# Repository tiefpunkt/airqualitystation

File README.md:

# Air Quality Station

Small outdoor particulate matter sensor. Measures PM1.0 and PM2.5, as well as temperature and humidity. Connects to an online service to show the measurements not only of one sensor, but all sensors in the area.

## Hardware
* ESP8266
* [Custom PCB](hardware/) (or your own whatever thingie)
* A bunch of small parts (TODO: Add BOM)
* DHT22 for temperature and humidity ([Grove Wiki](http://www.seeedstudio.com/wiki/Grove_-_Temperature_and_Humidity_Sensor_Pro))
* Shinyei PPD42NS for PM2.5 and PM1.0 ([Grove Wiki](http://www.seeedstudio.com/wiki/Grove_-_Dust_Sensor))

## Setup
* Solder up the PCB (PCBs might be for sale in the future, in the meantime look at the files [here](hardware/))
* Crimp the sensors to the connectors
* Put your WiFi credentials in the firmware
* Flash the firmware via the FTDI connector on the board (make sure it's set to 3.3V)
* Connect the sensors
* Put it all in a weatherproof box, that let's air in.
* Place it outside
* Power it up

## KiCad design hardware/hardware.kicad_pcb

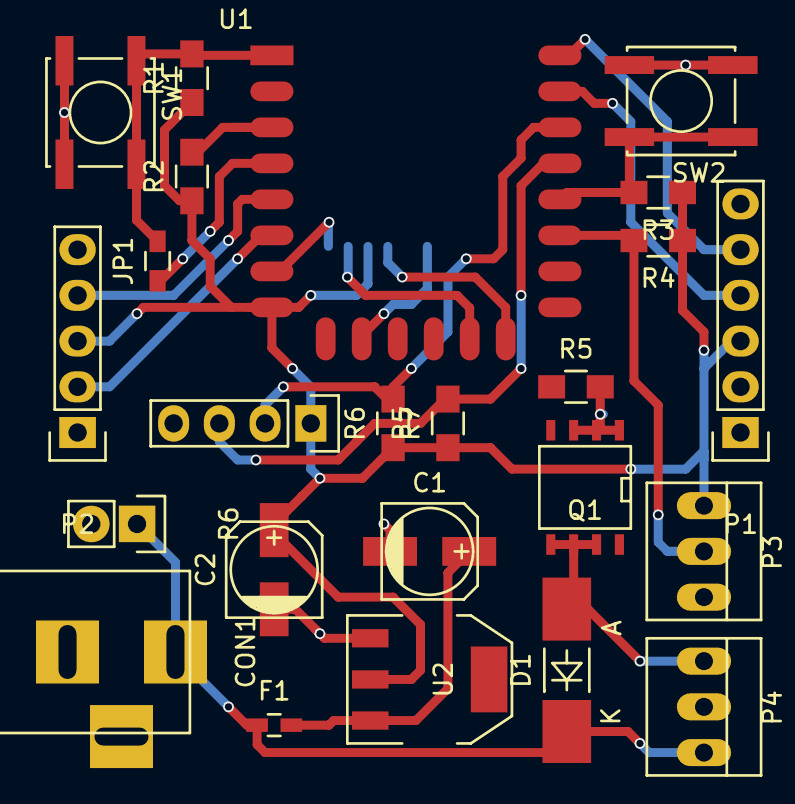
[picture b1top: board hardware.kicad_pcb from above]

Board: 2 copper layers, 25 parts (1 on the bottom side), 21 nets.

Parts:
C1, C2: 10µ; c_elec_5x5.3
CON1: BARREL_JACK
D1: D; MELF_Handsoldering
F1: 0.1A; C_0603_HandSoldering
J1: MicroSD; MICRO_SD_HINGE_AMP
JP1: Sleep; R_0603_HandSoldering
P1: FTDI ESP; Pin_Header_Straight_1x06
P2: PPD42NS; Pin_Header_Straight_1x05
P3: DHT22; PINHEAD1-3
P4: Fan; PINHEAD1-3
P5: I2C; Pin_Header_Straight_1x04
P6: CONN_01X02; Pin_Header_Straight_1x02
Q1: IRF7401; SOIC-8-N
R1, R2, R3, R4, R5, R6, R7: 10k; R_0805_HandSoldering
SW1: Reset; SW_SPST_EVPBF
SW2: Flash; SW_SPST_EVPBF
U1: ESP-12E
U2: TS 1117 BCW33; SOT-223

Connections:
+9V: CON1.1, D1.1, F1.1, P4.3, P6.1
GND: C1.2, C2.2, CON1.3, J1.6, J1.SHLD, P1.1, P2.1, P3.3, P5.4, P6.2, Q1.1, Q1.2, Q1.3, R5.2, SW1.2, SW2.2, U1.15, U2.1
unnamed: C1.1, F1.2, U2.3
unnamed: D1.2, P4.1, Q1.5, Q1.6, Q1.7
unnamed: J1.2, U1.7
unnamed: J1.3, U1.13
unnamed: J1.5, U1.14
unnamed: J1.7, U1.10
unnamed: JP1.1, U1.4
unnamed: JP1.2, R1.2, SW1.1, U1.1
unnamed: P1.4, U1.21
unnamed: P1.5, U1.22
unnamed: P2.2, U1.6
unnamed: P2.4, U1.5
unnamed: P3.2, R4.2, U1.17
unnamed: P5.2, R6.2, U1.20
unnamed: P5.3, R7.2, U1.19
unnamed: Q1.4, R5.1, U1.16
unnamed: R2.2, U1.3
unnamed: R3.2, SW2.1, U1.18
VCC: C2.1, J1.4, P1.3, P2.3, P3.1, P5.1, R1.1, R2.1, R3.1, R4.1, R6.1, R7.1, U1.8, U2.2

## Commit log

2015-10-09 initial linkit one port
2016-02-29 chaos pre_rewrite
2016-02-29 Firmware rewrite for ESP8266, using HTTP instead of MQTT
    Unit will only post to server, no need for messaging at the moment.
    Thus, it makes no sense to keep up an MQTT connection.
    HTTP/HTTPS will have to suffice. Using HTTP for now, should be
    an easy switch to HTTPS though.
2016-02-29 added rudimentary backend implementation
2016-08-10 schematic and pcb
2016-09-12 backend stuff, writer for nodes.json for meshviewer-air
2016-09-12 pcb of the first production run
2016-10-05 firmware with multi-ap
2016-11-05 added WiFi.mode(WIFI_STA) to connectWifi()
2016-11-06 - reactivated warum period after testing - changed DEBUG_PRINTLN to Serial.print to get MAC printed correctly at startup
